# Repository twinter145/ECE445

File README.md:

# ECE445
ECE 445 Senior Design Project LED Photography Light

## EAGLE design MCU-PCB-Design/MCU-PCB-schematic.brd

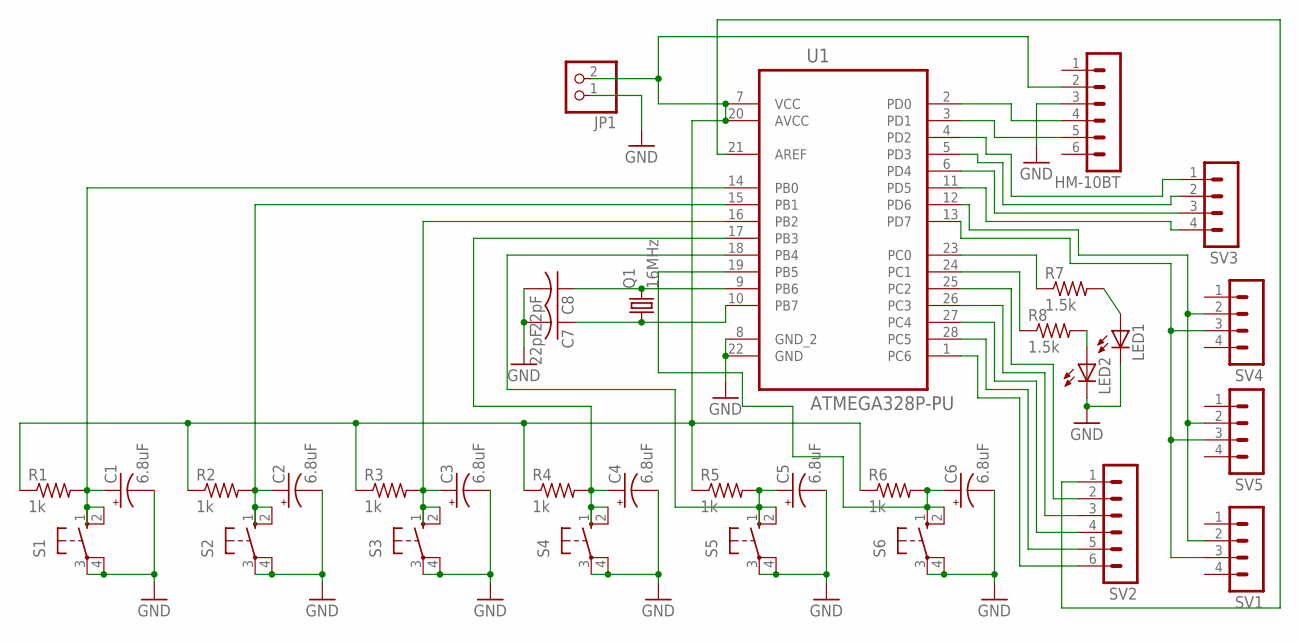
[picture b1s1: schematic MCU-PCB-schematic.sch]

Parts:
C1, C2, C3, C4, C5, C6: 6.8uF; E2,5-5
C7, C8: 22pF; C025-024X044
HM-10BT: MA06-1
JP1: PINHD-1X2; 1X02
LED1, LED2: LED5MM
Q1: 16MHz; HC49/S
R1, R2, R3, R4, R5, R6: 1k; 0207/10
R7, R8: 1.5k; 0207/10
S1, S2, S3, S4, S5, S6: 10-XX; B3F-10XX
SV1, SV3, SV4, SV5: MA04-1
SV2: MA06-1
U1: ATMEGA328P-PU; DIP254P762X457-28

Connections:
GND: C1.-, C2.-, C3.-, C4.-, C5.-, C6.-, C7.2, C8.2, HM-10BT.3, JP1.1, LED1.K (C), LED2.K (C), S1.3, S1.4 (P1), S2.3, S2.4 (P1), S3.3, S3.4 (P1), S4.3, S4.4 (P1), S5.3, S5.4 (P1), S6.3, S6.4 (P1), U1.8 (GND_2), U1.22 (GND)
unnamed: HM-10BT.2, JP1.2, R1.1, R2.1, R3.1, R4.1, R5.1, R6.1, U1.7 (VCC), U1.20 (AVCC)
unnamed: C1.+, R1.2, S1.1 (S), S1.2 (S1), U1.14 (PB0)
unnamed: C5.+, R5.2, S5.1 (S), S5.2 (S1), U1.18 (PB4)
unnamed: C6.+, R6.2, S6.1 (S), S6.2 (S1), U1.19 (PB5)
unnamed: C8.1, Q1.2, U1.9 (PB6)
unnamed: C7.1, Q1.1, U1.10 (PB7)
unnamed: HM-10BT.4, U1.2 (PD0)
unnamed: HM-10BT.5, U1.3 (PD1)
unnamed: R7.1, U1.23 (PC0)
unnamed: R8.1, U1.24 (PC1)
unnamed: LED1.A, R7.2
unnamed: LED2.A, R8.2
unnamed: SV1.3, SV4.3, SV5.3, U1.13 (PD7)
unnamed: SV1.2, SV4.2, SV5.2, U1.12 (PD6)
unnamed: SV2.2, U1.25 (PC2)
unnamed: SV2.3, U1.26 (PC3)
unnamed: SV2.4, U1.27 (PC4)
unnamed: SV2.5, U1.28 (PC5)
unnamed: SV2.6, U1.1 (PC6)
unnamed: SV2.1, U1.21 (AREF)
unnamed: C3.+, R3.2, S3.1 (S), S3.2 (S1), U1.16 (PB2)
unnamed: SV3.2, U1.5 (PD3)
unnamed: SV3.3, U1.6 (PD4)
unnamed: SV3.4, U1.11 (PD5)
unnamed: SV3.1, U1.4 (PD2)
unnamed: C2.+, R2.2, S2.1 (S), S2.2 (S1), U1.15 (PB1)
unnamed: C4.+, R4.2, S4.1 (S), S4.2 (S1), U1.17 (PB3)

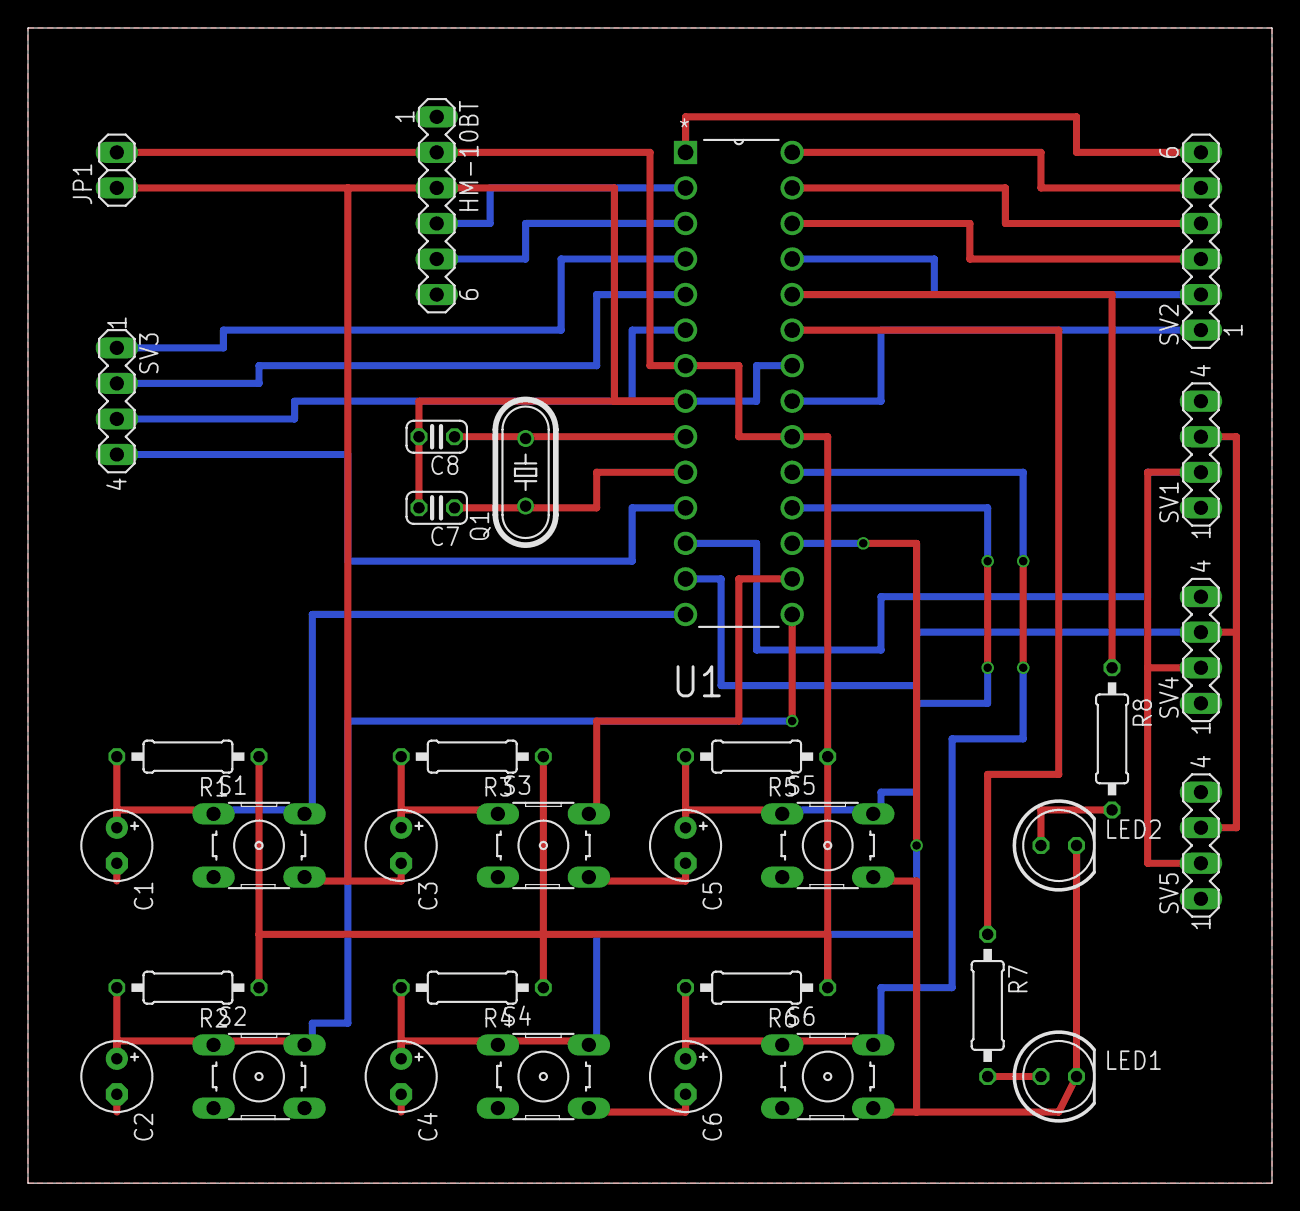
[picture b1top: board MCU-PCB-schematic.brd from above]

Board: 2 copper layers, 88.9 x 82.5 mm, 33 parts (0 on the bottom side), 28 nets.

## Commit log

2023-06-06 add project files
2023-06-06 add pcb design
